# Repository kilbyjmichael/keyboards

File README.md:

# keyboards
to hold all my crappy keyboard designs

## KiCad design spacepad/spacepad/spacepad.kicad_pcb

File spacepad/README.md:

# SpacePad

A macropad/numpad inspired by a ship control panel

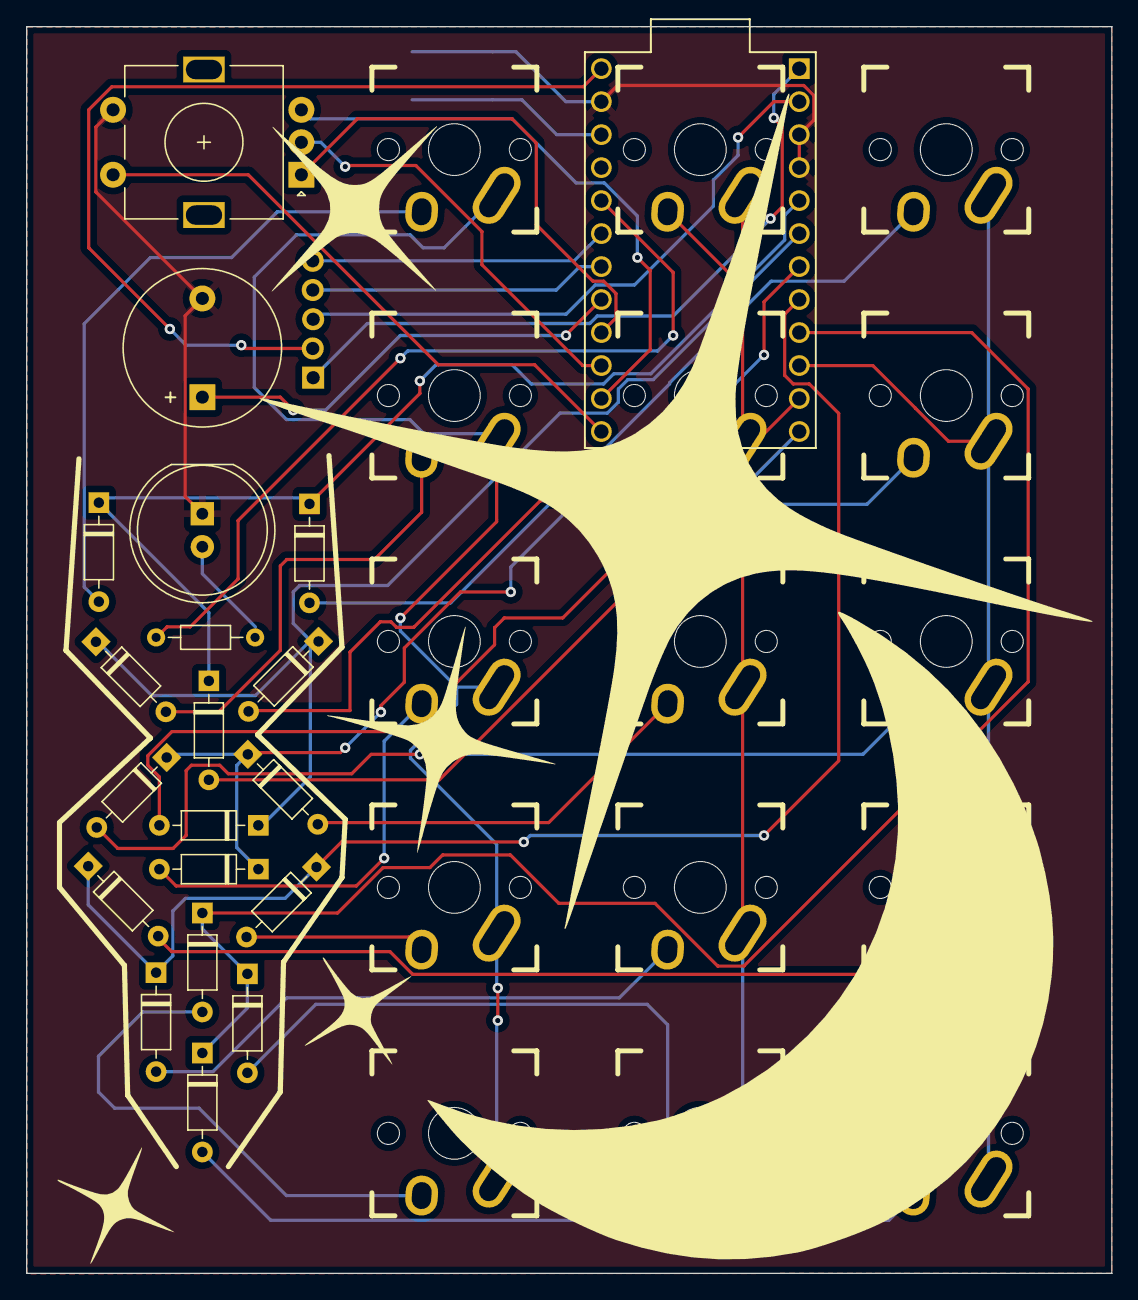
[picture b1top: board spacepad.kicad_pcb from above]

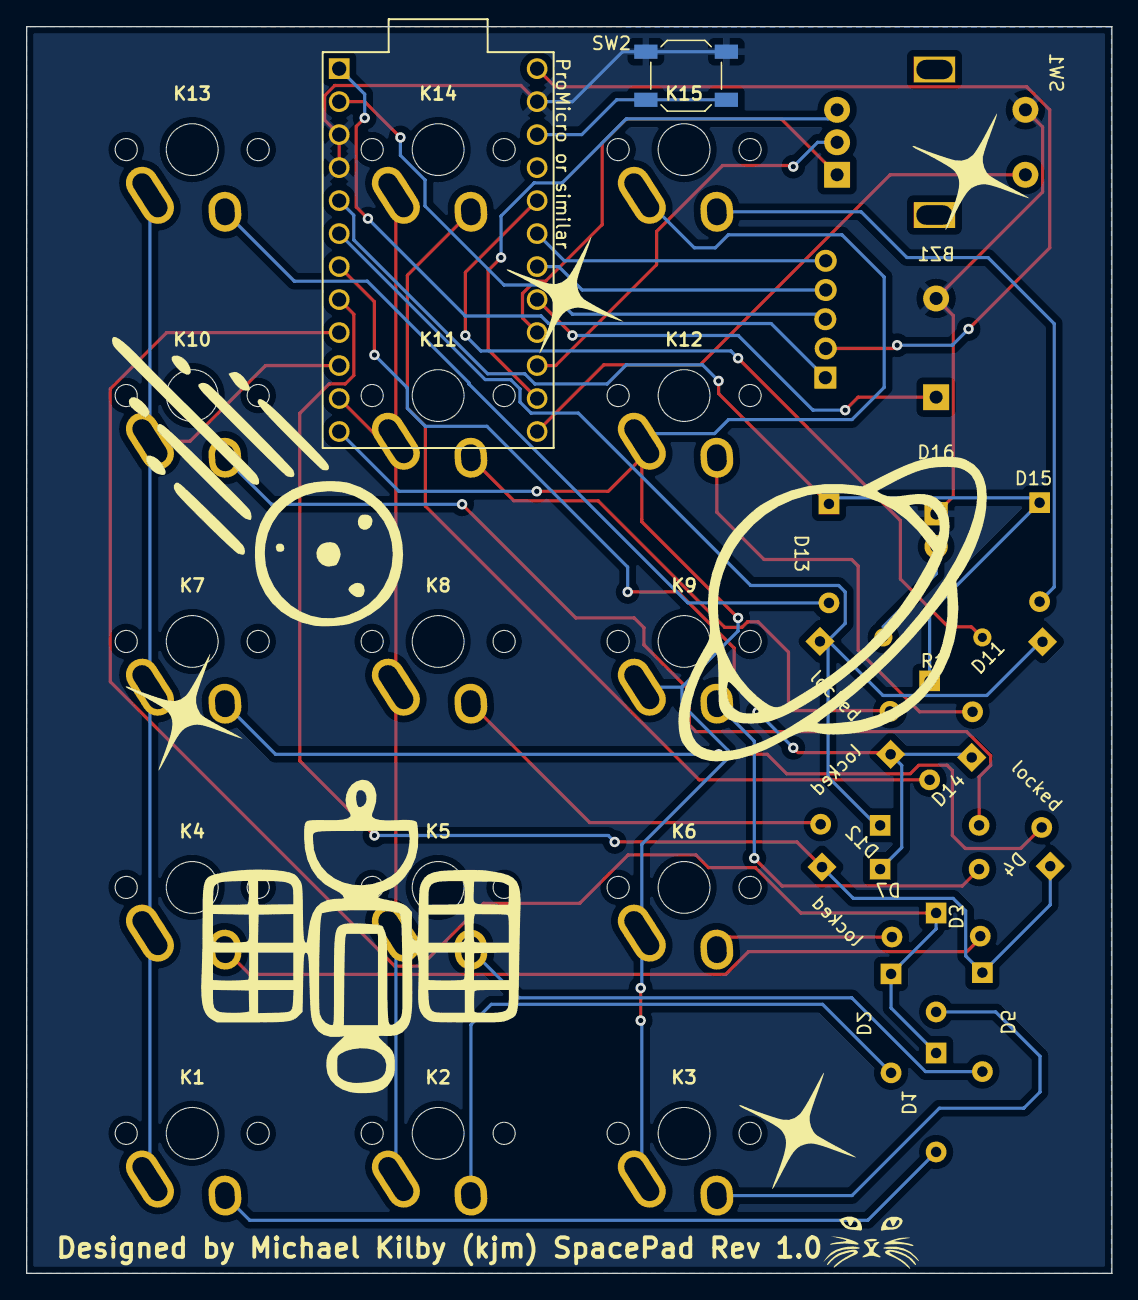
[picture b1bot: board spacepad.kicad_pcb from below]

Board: 2 copper layers, 83.6 x 96.0 mm, 41 parts (2 on the bottom side), 37 nets.

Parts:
BZ1: Buzzer; Buzzer_12x9.5RM7.6
D1, D2, D3, D4, D5, D7, D11, D12, D14, D15: 1N4148; D_DO-35_SOD27_P7.62mm_Horizontal
D13: locked; D_DO-35_SOD27_P7.62mm_Horizontal
D16: LED; LED_D10.0mm
J1, J3, J4, J5: Conn_01x01_Female; PIN_1
J2: Conn_01x01_Female; PIN_1_SQUARE
K1, K2, K3, K4, K5, K6, K7, K8, K9, K10, K11, K12, K13, K14, K15: KEYSW; Mx_Alps_100
ProMicro or similar: ProMicro
R1: R; R_Axial_DIN0204_L3.6mm_D1.6mm_P7.62mm_Horizontal
SW1: RotaryEncoder_Switch; RotaryEncoder_Alps_EC11E-Switch_Vertical_H20mm
SW2: SW_PUSH; SW_SPST_SKQG_WithoutStem
locked: locked; D_DO-35_SOD27_P7.62mm_Horizontal
locked#2, locked#3: locked; D_DO-35_SOD27_P7.62mm_Horizontal
locked#4: 1N4148; D_DO-35_SOD27_P7.62mm_Horizontal

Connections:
GND: BZ1.2 (+), D16.1 (K), ProMicro or similar.3 (GND), ProMicro or similar.4 (GND), ProMicro or similar.23 (GND), SW1.S1, SW2.2
unnamed: BZ1.1 (-), ProMicro or similar.17 (F7)
unnamed: D1.1 (K), D2.1 (K), D3.1 (K), ProMicro or similar.9 (D7)
unnamed: D1.2 (A), K1.2
unnamed: D2.2 (A), K2.2
unnamed: D3.2 (A), K3.2
unnamed: D4.1 (K), D5.1 (K), ProMicro or similar.8 (C6), locked#3.1 (K)
unnamed: D4.2 (A), K4.2
unnamed: D5.2 (A), K5.2
unnamed: K6.2, locked#3.2 (A)
unnamed: D7.1 (K), ProMicro or similar.7 (D4), locked.1 (K), locked#4.1 (K)
unnamed: D7.2 (A), K9.2
unnamed: K7.2, locked#4.2 (A)
unnamed: K8.2, locked.2 (A)
unnamed: D11.1 (K), D12.1 (K), ProMicro or similar.6 (SCL), locked#2.1 (K)
unnamed: K11.2, locked#2.2 (A)
unnamed: D11.2 (A), K12.2
unnamed: D12.2 (A), K10.2
unnamed: D13.1 (K), D14.1 (K), D15.1 (K), ProMicro or similar.5 (SDA)
unnamed: D13.2 (A), K13.2
unnamed: D14.2 (A), K14.2
unnamed: D15.2 (A), K15.2
unnamed: D16.2 (A), R1.2
unnamed: J1.1, ProMicro or similar.2 (RX)
unnamed: J2.1, ProMicro or similar.1 (TX)
unnamed: J3.1, ProMicro or similar.24 (RAW)
unnamed: J4.1, ProMicro or similar.19 (F5)
unnamed: J5.1, ProMicro or similar.18 (F6)
unnamed: K1.1, K4.1, K7.1, K10.1, K13.1, ProMicro or similar.10 (E6)
unnamed: K2.1, K5.1, K8.1, K11.1, K14.1, ProMicro or similar.11 (B4)
unnamed: K3.1, K6.1, K9.1, K12.1, K15.1, ProMicro or similar.12 (B5)
unnamed: ProMicro or similar.20 (F4), R1.1
unnamed: ProMicro or similar.16 (B1), SW1.A
unnamed: ProMicro or similar.14 (B2), SW1.B
unnamed: ProMicro or similar.15 (B3), SW1.C
unnamed: ProMicro or similar.13 (B6), SW1.S2
unnamed: ProMicro or similar.22 (RST), SW2.1
